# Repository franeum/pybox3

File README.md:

# pybox3

## dependencies

- neopixel.mpy
- simpleio.mpy
- adafruit_framebuf.mpy
- adafruit_pixel_framebuf.mpy
- adafruit_midi
- adafruit_waveform

### 
1. call callback with an implicit argument

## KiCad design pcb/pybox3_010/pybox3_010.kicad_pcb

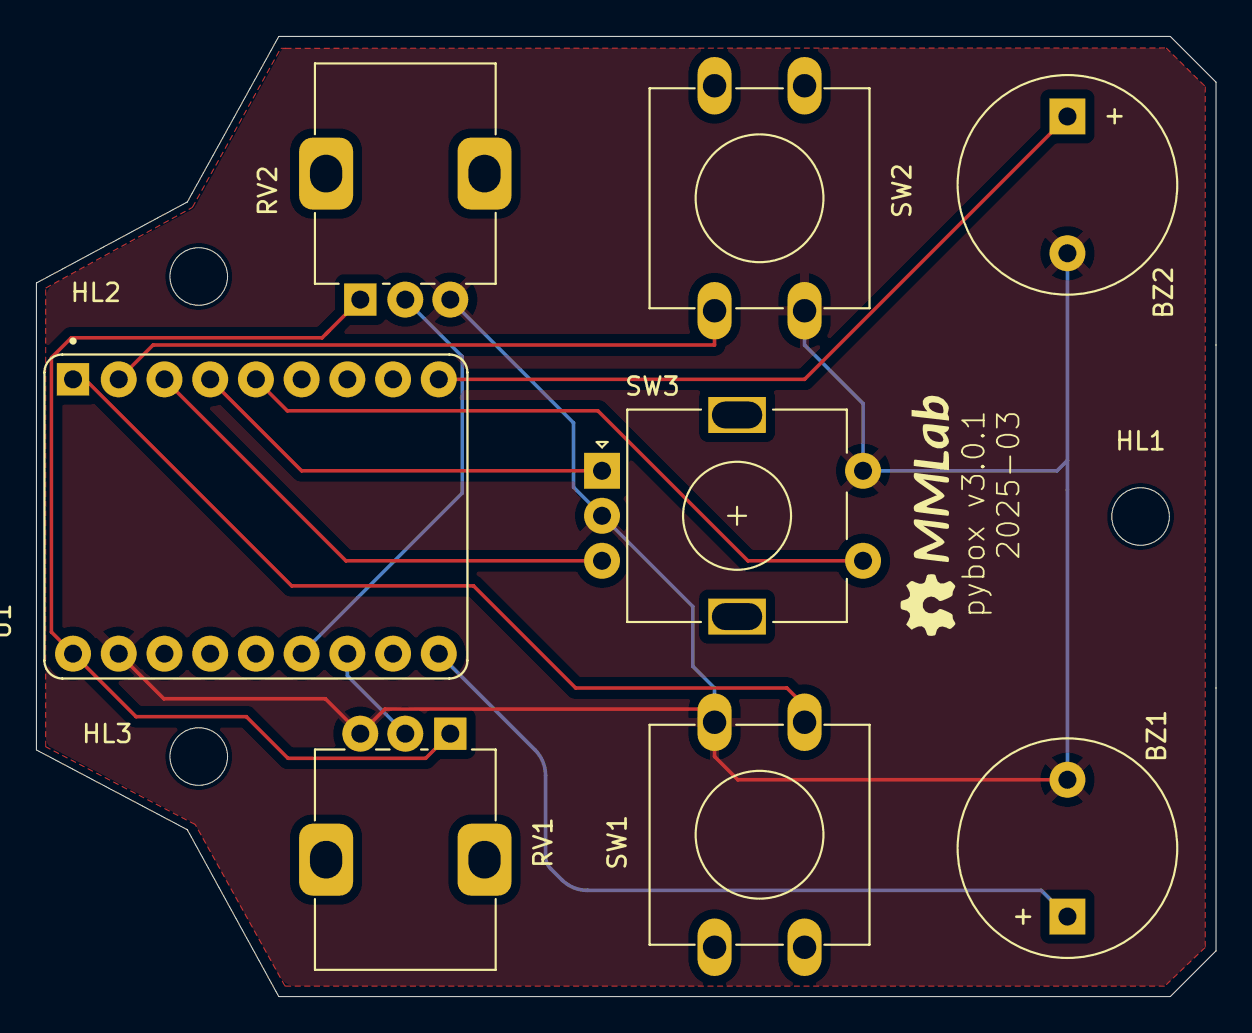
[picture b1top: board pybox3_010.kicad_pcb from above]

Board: 2 copper layers, 65.5 x 53.3 mm, 11 parts (0 on the bottom side), 11 nets.

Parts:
BZ1, BZ2: Buzzer; Buzzer_12x9.5RM7.6
HL1, HL2, HL3: MountingHole_3.2mm_M3
RV1, RV2: R_Potentiometer; Potentiometer_Alps_RK09K_Single_Vertical
SW1, SW2: SW_Push; SW_PUSH-12mm
SW3: RotaryEncoder_Switch; RotaryEncoder_Alps_EC11E-Switch_Vertical_H20mm
U1: RP2040-ZERO; MODULE_RP2040-ZERO_reduced

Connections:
GND: BZ1.2 (-), BZ2.2 (-), RV1.3, RV2.3, SW1.1, SW2.1, SW3.C, SW3.S2, U1.22 (GND)
unnamed: BZ1.1 (+), U1.15 (GP14)
unnamed: BZ2.1 (+), U1.9 (GP8)
unnamed: SW1.2, U1.1 (GP0)
unnamed: SW2.2, U1.2 (GP1)
unnamed: SW3.B, U1.3 (GP2)
unnamed: SW3.A, U1.4 (GP3)
unnamed: SW3.S1, U1.5 (GP4)
unnamed: RV1.2, U1.17 (GP26)
unnamed: RV2.2, U1.18 (GP27)
VCC: RV1.1, RV2.1, U1.23 (5V)

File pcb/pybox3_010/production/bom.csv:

Designator,Footprint,Quantity,Value,LCSC Part #
"BZ1, BZ2",Buzzer_12x9.5RM7.6,2,Buzzer,
"RV1, RV2",Potentiometer_Alps_RK09K_Single_Vertical,2,R_Potentiometer,
"SW1, SW2",SW_PUSH-12mm,2,SW_Push,
SW3,RotaryEncoder_Alps_EC11E-Switch_Vertical_H20mm,1,RotaryEncoder_Switch,
U1,MODULE_RP2040-ZERO_reduced,1,RP2040-ZERO,

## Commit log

2025-03-05 ADDED
2025-03-05 ADDED; TODO: better smoothing algorithm on value() method
2025-03-05 update smoothing (but not perfect)
2025-03-05 ADDED: not asyncronous, so you cannot do polyphony. Review simpleio, perhaps it would be used another lib
2025-03-05 deleted
2025-03-10 IMPLEMENTED: PIXEL class
2025-03-10 FIXED: substituted 5V with 3V3 power pin
2025-03-10 FIXED: new pcb ready (3.0.1)
2025-03-10 updated: production files
2025-03-10 FIXED: set terminal (mkdocs-terminal)
2025-03-12 ADD: cc() method && docstrings
2025-04-07 ADD: dependencies
2025-04-07 FIX: inserted default color to RED, instead None
2025-04-07 ADD: update mpy files to the board
2025-04-22 deploy: 6b3eb13f6837178ba75b0b939038cf8847b93d1a
2025-09-10 FIX: toggle() in PIXEL class. Now it runs on every pixel in the matrix
2025-09-10 deploy: aa987bfff00b2b15b395920e83685c9517683618
2025-09-10 FIX: indexing of buttons in BUTTON class. Now you can call it by index (and not by board.pin)
2025-09-10 deploy: 4871cdb62b3971b3db99c7bfe18e69a9ee27277d
2025-09-30 deploy: 63f9b4b110cb9882fdd432357141378f2bd7eac2
2025-09-30 deploy: 4fceeefe8bcec970adf7d0e44e2d7d55fa06f22d
2025-09-30 deploy: 96fd5f2c12953f8b12129d1f55a342a3d1638edc
2025-09-30 deploy: 6761955fc0b619849d4a9b282f690a0e49a29709
2025-09-30 deploy: 3cb75dce621332c35971e99b75f9b71d867ae06b
2025-10-07 deploy: a04ca002fc0c7b4d33a6462fc535287d5a0cd042
